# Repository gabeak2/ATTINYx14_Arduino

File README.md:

# ATTINYx14_Arduino
An arduino-style breakout PCB for the ATTINY-x14 line of chips (specifically designed with the ATTINY1614).  Includes USB-Serial converter and USB connector so it is pretty much plug-and-play once you flash megatinycore onto it.

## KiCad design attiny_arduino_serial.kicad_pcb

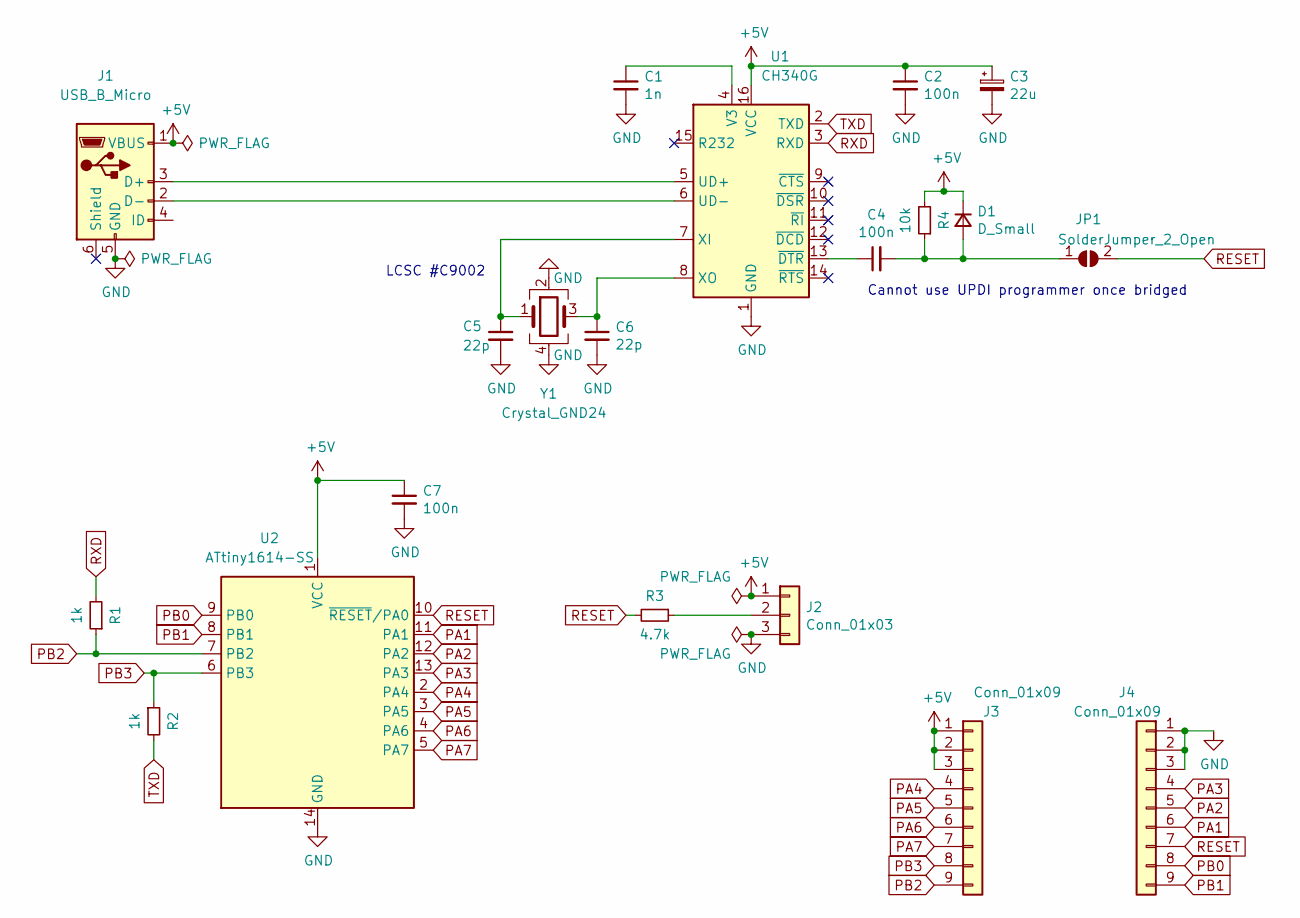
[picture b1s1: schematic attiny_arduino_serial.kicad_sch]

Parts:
C1: 1n; C_0805_2012Metric_Pad1.18x1.45mm_HandSolder
C2, C4, C7: 100n; C_0805_2012Metric_Pad1.18x1.45mm_HandSolder
C3: 22u; C_0805_2012Metric_Pad1.18x1.45mm_HandSolder
C5, C6: 22p; C_0805_2012Metric_Pad1.18x1.45mm_HandSolder
D1: D_Small; D_SOD-123
J1: USB_B_Micro; USB_Micro-B_Molex-105017-0001
J2: Conn_01x03; PinSocket_1x03_P2.54mm_Vertical
J3, J4: Conn_01x09; PinSocket_1x09_P2.54mm_Vertical
JP1: SolderJumper_2_Open; SolderJumper-2_P1.3mm_Open_Pad1.0x1.5mm
R1, R2: 1k; R_0805_2012Metric_Pad1.20x1.40mm_HandSolder
R3: 4.7k; R_0805_2012Metric_Pad1.20x1.40mm_HandSolder
R4: 10k; R_0805_2012Metric_Pad1.20x1.40mm_HandSolder
U1: CH340G; SOIC-16_3.9x9.9mm_P1.27mm
U2: ATtiny1614-SS; SOIC-14_3.9x8.7mm_P1.27mm
Y1: Crystal_GND24; Crystal_SMD_3225-4Pin_3.2x2.5mm_HandSoldering

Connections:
+5V: C2.1, C3.1, C7.1, D1.1 (K), J1.1 (VBUS), J2.1, J3.1, J3.2, J3.3, R4.2, U1.16 (VCC), U2.1 (VCC)
GND: C1.2, C2.2, C3.2, C5.2, C6.2, C7.2, J1.5 (GND), J2.3, J4.1, J4.2, J4.3, U1.1 (GND), U2.14 (GND), Y1.2, Y1.4
unnamed: C1.1, U1.4 (V3)
unnamed: C4.1, U1.13 (~DTR)
unnamed: C4.2, D1.2 (A), JP1.1 (A), R4.1
unnamed: C5.1, U1.7 (XI), Y1.1
unnamed: C6.1, U1.8 (XO), Y1.3
unnamed: J1.2 (D-), U1.6 (UD-)
unnamed: J1.3 (D+), U1.5 (UD+)
unnamed: J2.2, R3.1
PA1: J4.6, U2.11 (PA1)
PA2: J4.5, U2.12 (PA2)
PA3: J4.4, U2.13 (PA3)
PA4: J3.4, U2.2 (PA4)
PA5: J3.5, U2.3 (PA5)
PA6: J3.6, U2.4 (PA6)
PA7: J3.7, U2.5 (PA7)
PB0: J4.8, U2.9 (PB0)
PB1: J4.9, U2.8 (PB1)
PB2: J3.9, R1.1, U2.7 (PB2)
PB3: J3.8, R2.1, U2.6 (PB3)
RESET: J4.7, JP1.2 (B), R3.2, U2.10 (~RESET/PA0)
RXD: R1.2, U1.3 (RXD)
TXD: R2.2, U1.2 (TXD)

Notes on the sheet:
LCSC #C9002
Cannot use UPDI programmer once bridged

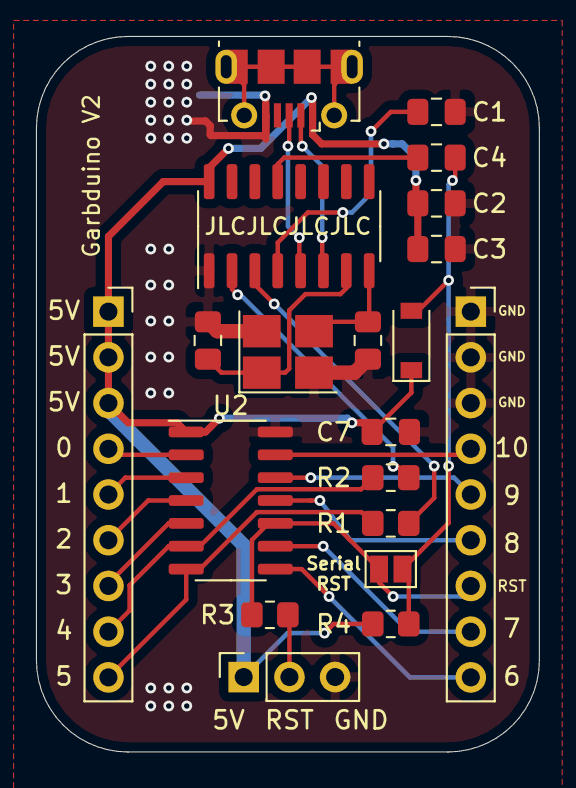
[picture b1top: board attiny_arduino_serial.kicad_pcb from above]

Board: 2 copper layers, 27.9 x 39.8 mm, 20 parts (0 on the bottom side), 24 nets.

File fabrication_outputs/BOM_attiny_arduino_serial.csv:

Comment,Designator,Footprint,LCSC Part Number
10k,R4,805,C17414
D_Small,D1,SOD-123,C8598
Crystal_GND24,Y1,3225-4,C9002
CH340G,U1,SOIC-16_3.9x9.9mm_P1.27mm,C14267
4.7k,R3,805,C17673
1k,"R2,R1",805,C17513
USB_B_Micro,J1,USB_Micro-B_Molex-105017-0001,C404969
100n,"C7,C4,C2",805,C49678
22p,"C6,C5",805,C1804
22u,C3,805,C45783
1n,C1,805,C46653
